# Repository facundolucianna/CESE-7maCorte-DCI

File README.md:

# CESE-7maCorte-DCI

Replica de Sparkfun ESP32 Thing. 

Basado de SparkFun ESP32 Thing (https://www.sparkfun.com/products/13907) 

Bajo Licencia Creative Commons Attributions Share-Alike 4.0 (https://creativecommons.org/licenses/by-sa/4.0/)

Modificación sin el respaldo del autor original

Atención:

Este diseño de PCB y esquematico se entrega "como está" y sin niguna garantia expresa o implícita, incluyendo, sin limitación, las garantias implícitas de comercialización y aptitude para un propósito particular.

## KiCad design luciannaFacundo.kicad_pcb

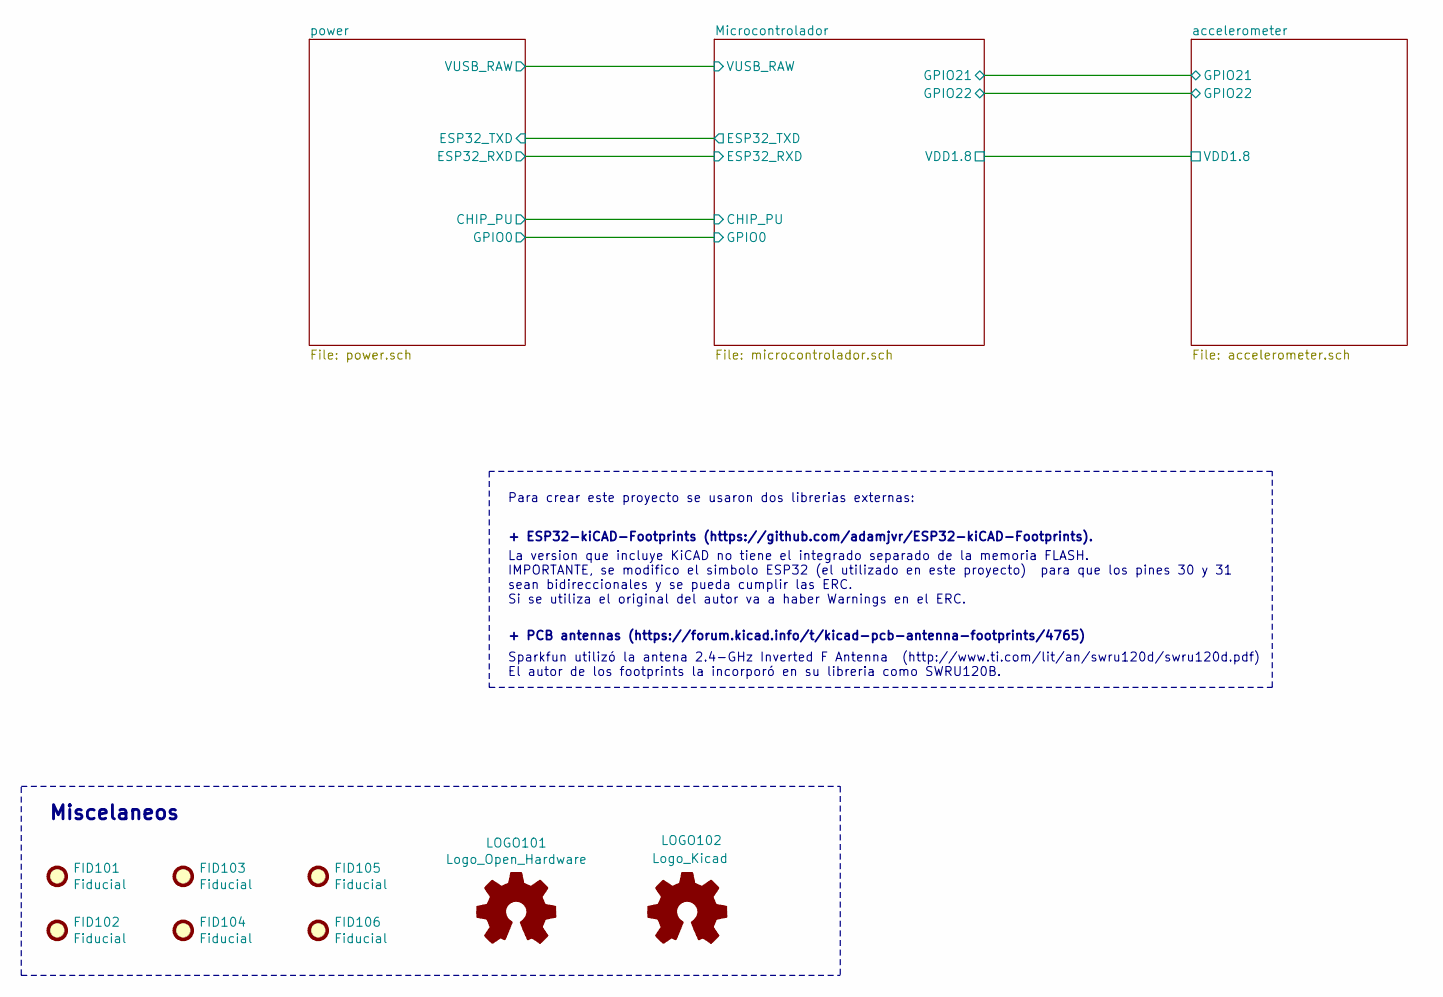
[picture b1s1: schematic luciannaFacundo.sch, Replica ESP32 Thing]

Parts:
FID101, FID102, FID103, FID104, FID105, FID106: Fiducial; Fiducial_1mm_Mask3mm
LOGO101: Logo_Open_Hardware; OSHW-Logo2_7.3x6mm_SilkScreen
LOGO102: Logo_Kicad; KiCad-Logo2_5mm_SilkScreen

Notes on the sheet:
Para crear este proyecto se usaron dos librerias externas: La version que incluye KiCAD no tiene el integrado separado de la memoria FLASH. IMPORTANTE, se modifico el simbolo ESP32 (el utilizado en este proyecto) para que los pines 30 y 31 sean bidireccionales y se pueda cumplir las ERC. Si se util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
+ ESP32-kiCAD-Footprints (https://github.com/adamjvr/ESP32-kiCAD-Footprints).
+ PCB antennas (https://forum.kicad.info/t/kicad-pcb-antenna-footprints/4765)
Miscelaneos

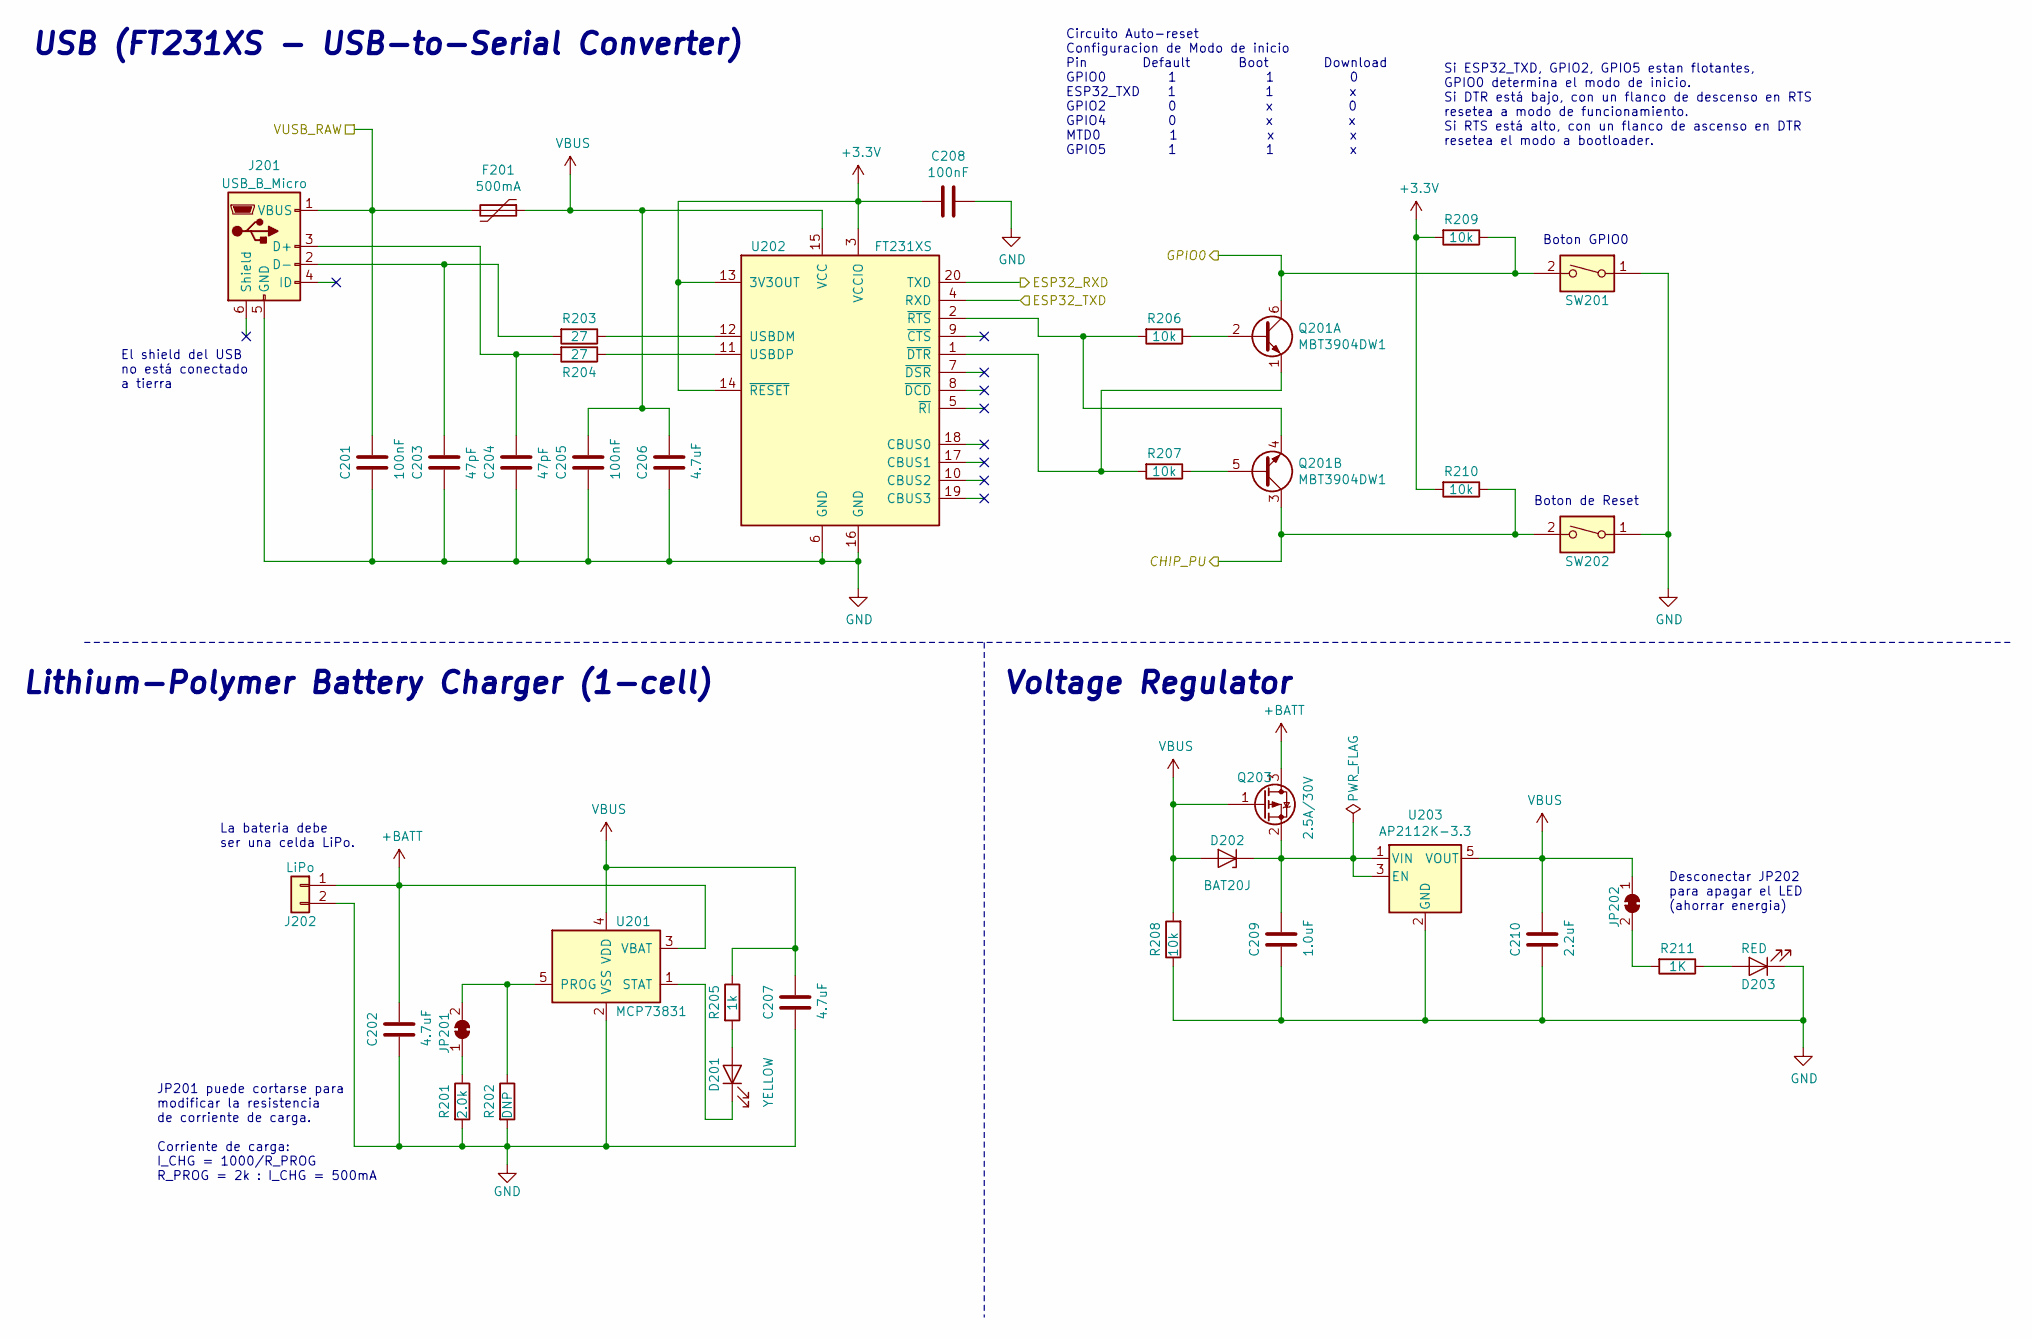
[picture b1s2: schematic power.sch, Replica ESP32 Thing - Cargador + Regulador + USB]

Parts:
C201, C205, C208: 100nF; C_0603_1608Metric
C202, C206, C207: 4.7uF; C_0603_1608Metric
C203, C204: 47pF; C_0603_1608Metric
C209: 1.0uF; C_0805_2012Metric
C210: 2.2uF; C_0603_1608Metric
D201: YELLOW; LED_0603_1608Metric
D202: BAT20J; D_SOD-323
D203: RED; LED_0603_1608Metric
F201: 500mA; Fuse_1206_3216Metric
J201: USB_B_Micro; USB_Micro-B_Wuerth_629105150521
J202: LiPo; JST_PH_S2B-PH-K_1x02_P2.00mm_Horizontal
JP201, JP202: SolderJumper_2_Bridged; SolderJumper-2_P1.3mm_Bridged2Bar_RoundedPad1.0x1.5mm
Q201: MBT3904DW1; SOT-363_SC-70-6
Q203: 2.5A/30V; SOT-23
R201: 2.0k; R_0603_1608Metric
R202: DNP; R_Axial_DIN0204_L3.6mm_D1.6mm_P5.08mm_Horizontal
R203, R204: 27; R_0603_1608Metric
R205: 1k; R_0603_1608Metric
R206, R207, R208, R209, R210: 10k; R_0603_1608Metric
R211: 1K; R_0603_1608Metric
SW201, SW202: SW_DIP_x01; SW_Push_1P1T_NO_CK_KMR2
U201: MCP73831; SOT-23-5
U202: FT231XS; SSOP-20_3.9x8.7mm_P0.635mm
U203: AP2112K-3.3; SOT-23-5

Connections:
+3V3: C208.2, R209.2, R210.2, U202.3 (VCCIO), U202.13 (3V3OUT), U202.14 (~RESET); also elsewhere on the board
+BATT: C202.1, J202.1, Q203.3 (D), U201.3 (VBAT); also elsewhere on the board
CHIP_PU: Q201.3 (C2), R210.1, SW202.2; also elsewhere on the board
ESP32_RXD: U202.20 (TXD); also elsewhere on the board
ESP32_TXD: U202.4 (RXD); also elsewhere on the board
GND: C201.2, C202.2, C203.2, C204.2, C205.2, C206.2, C207.2, C208.1, C209.2, C210.2, D203.1 (K), J201.5 (GND), J201.6 (Shield), J202.2, R201.2, R202.2, R208.1, SW201.1, SW202.1, U201.2 (VSS), U202.6 (GND), U202.16 (GND), U203.2 (GND); also elsewhere on the board
GPIO0: Q201.6 (C1), R209.1, SW201.2; also elsewhere on the board
unnamed: C203.1, J201.2 (D-), R203.2
unnamed: C204.1, J201.3 (D+), R204.2
unnamed: C209.1, D202.1 (K), Q203.2 (S), U203.1 (VIN), U203.3 (EN)
unnamed: D201.1 (K), U201.1 (STAT)
unnamed: D203.2 (A), R211.1
unnamed: JP201.1 (A), R201.1
unnamed: JP201.2 (B), R202.1, U201.5 (PROG)
unnamed: JP202.2 (B), R211.2
unnamed: Q201.1 (E1), R207.2, U202.1 (~DTR)
unnamed: Q201.2 (B1), R206.1
unnamed: Q201.4 (E2), R206.2, U202.2 (~RTS)
unnamed: Q201.5 (B2), R207.1
unnamed: R203.1, U202.12 (USBDM)
unnamed: R204.1, U202.11 (USBDP)
VUSB_RAW: C201.1, F201.2, J201.1 (VBUS); also elsewhere on the board

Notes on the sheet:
Circuito Auto-reset Configuracion de Modo de inicio Pin Default Boot Download GPIO0 1 1 0 ESP32_TXD 1 1 x GPIO2 0 x 0 GPIO4 0 x x MTD0 1 x x GPIO5 1 1 x
La bateria debe ser una celda LiPo.
JP201 puede cortarse para modificar la resistencia de corriente de carga. Corriente de carga: I_CHG = 1000/R_PROG R_PROG = 2k : I_CHG = 500mA
Desconectar JP202 para apagar el LED (ahorrar energia)
USB (FT231XS - USB-to-Serial Converter)
Lithium-Polymer Battery Charger (1-cell)
Voltage Regulator
Si ESP32_TXD, GPIO2, GPIO5 estan flotantes, GPIO0 determina el modo de inicio. Si DTR está bajo, con un flanco de descenso en RTS resetea a modo de funcionamiento. Si RTS está alto, con un flanco de ascenso en DTR resetea el modo a bootloader.
Boton GPIO0
Boton de Reset
El shield del USB no está conectado a tierra

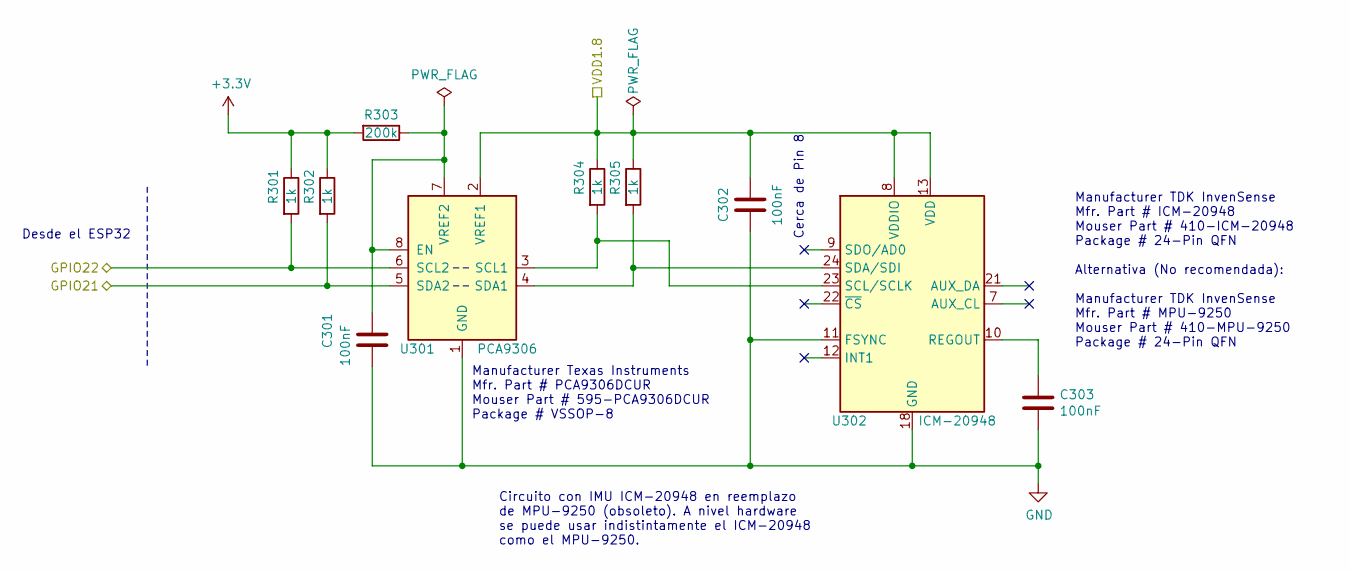
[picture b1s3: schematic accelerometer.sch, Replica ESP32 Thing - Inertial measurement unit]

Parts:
C301, C302, C303: 100nF; C_0603_1608Metric
R301, R302, R304, R305: 1k; R_0603_1608Metric
R303: 200k; R_0603_1608Metric
U301: PCA9306; VSSOP-8_2.3x2mm_P0.5mm
U302: ICM-20948; InvenSense_QFN-24_3x3mm_P0.4mm

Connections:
+3V3: R301.1, R302.1, R303.2; also elsewhere on the board
GND: C301.2, C302.2, C303.2, U301.1 (GND), U302.11 (FSYNC), U302.18 (GND), U302.20 (GND); also elsewhere on the board
GPIO21: R302.2, U301.5 (SDA2); also elsewhere on the board
GPIO22: R301.2, U301.6 (SCL2); also elsewhere on the board
unnamed: C301.1, R303.1, U301.7 (VREF2), U301.8 (EN)
unnamed: C303.1, U302.10 (REGOUT)
unnamed: R304.2, U301.3 (SCL1), U302.23 (SCL/SCLK)
unnamed: R305.2, U301.4 (SDA1), U302.24 (SDA/SDI)
VDD1.8: C302.1, R304.1, R305.1, U301.2 (VREF1), U302.8 (VDDIO), U302.13 (VDD); also elsewhere on the board

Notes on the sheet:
Cerca de Pin 8
Circuito con IMU ICM-20948 en reemplazo de MPU-9250 (obsoleto). A nivel hardware se puede usar indistintamente el ICM-20948 como el MPU-9250.
Desde el ESP32
Manufacturer Texas Instruments Mfr. Part # PCA9306DCUR Mouser Part # 595-PCA9306DCUR Package # VSSOP-8
Manufacturer TDK InvenSense Mfr. Part # ICM-20948 Mouser Part # 410-ICM-20948 Package # 24-Pin QFN Alternativa (No recomendada): Manufacturer TDK InvenSense Mfr. Part # MPU-9250 Mouser Part # 410-MPU-9250 Package # 24-Pin QFN

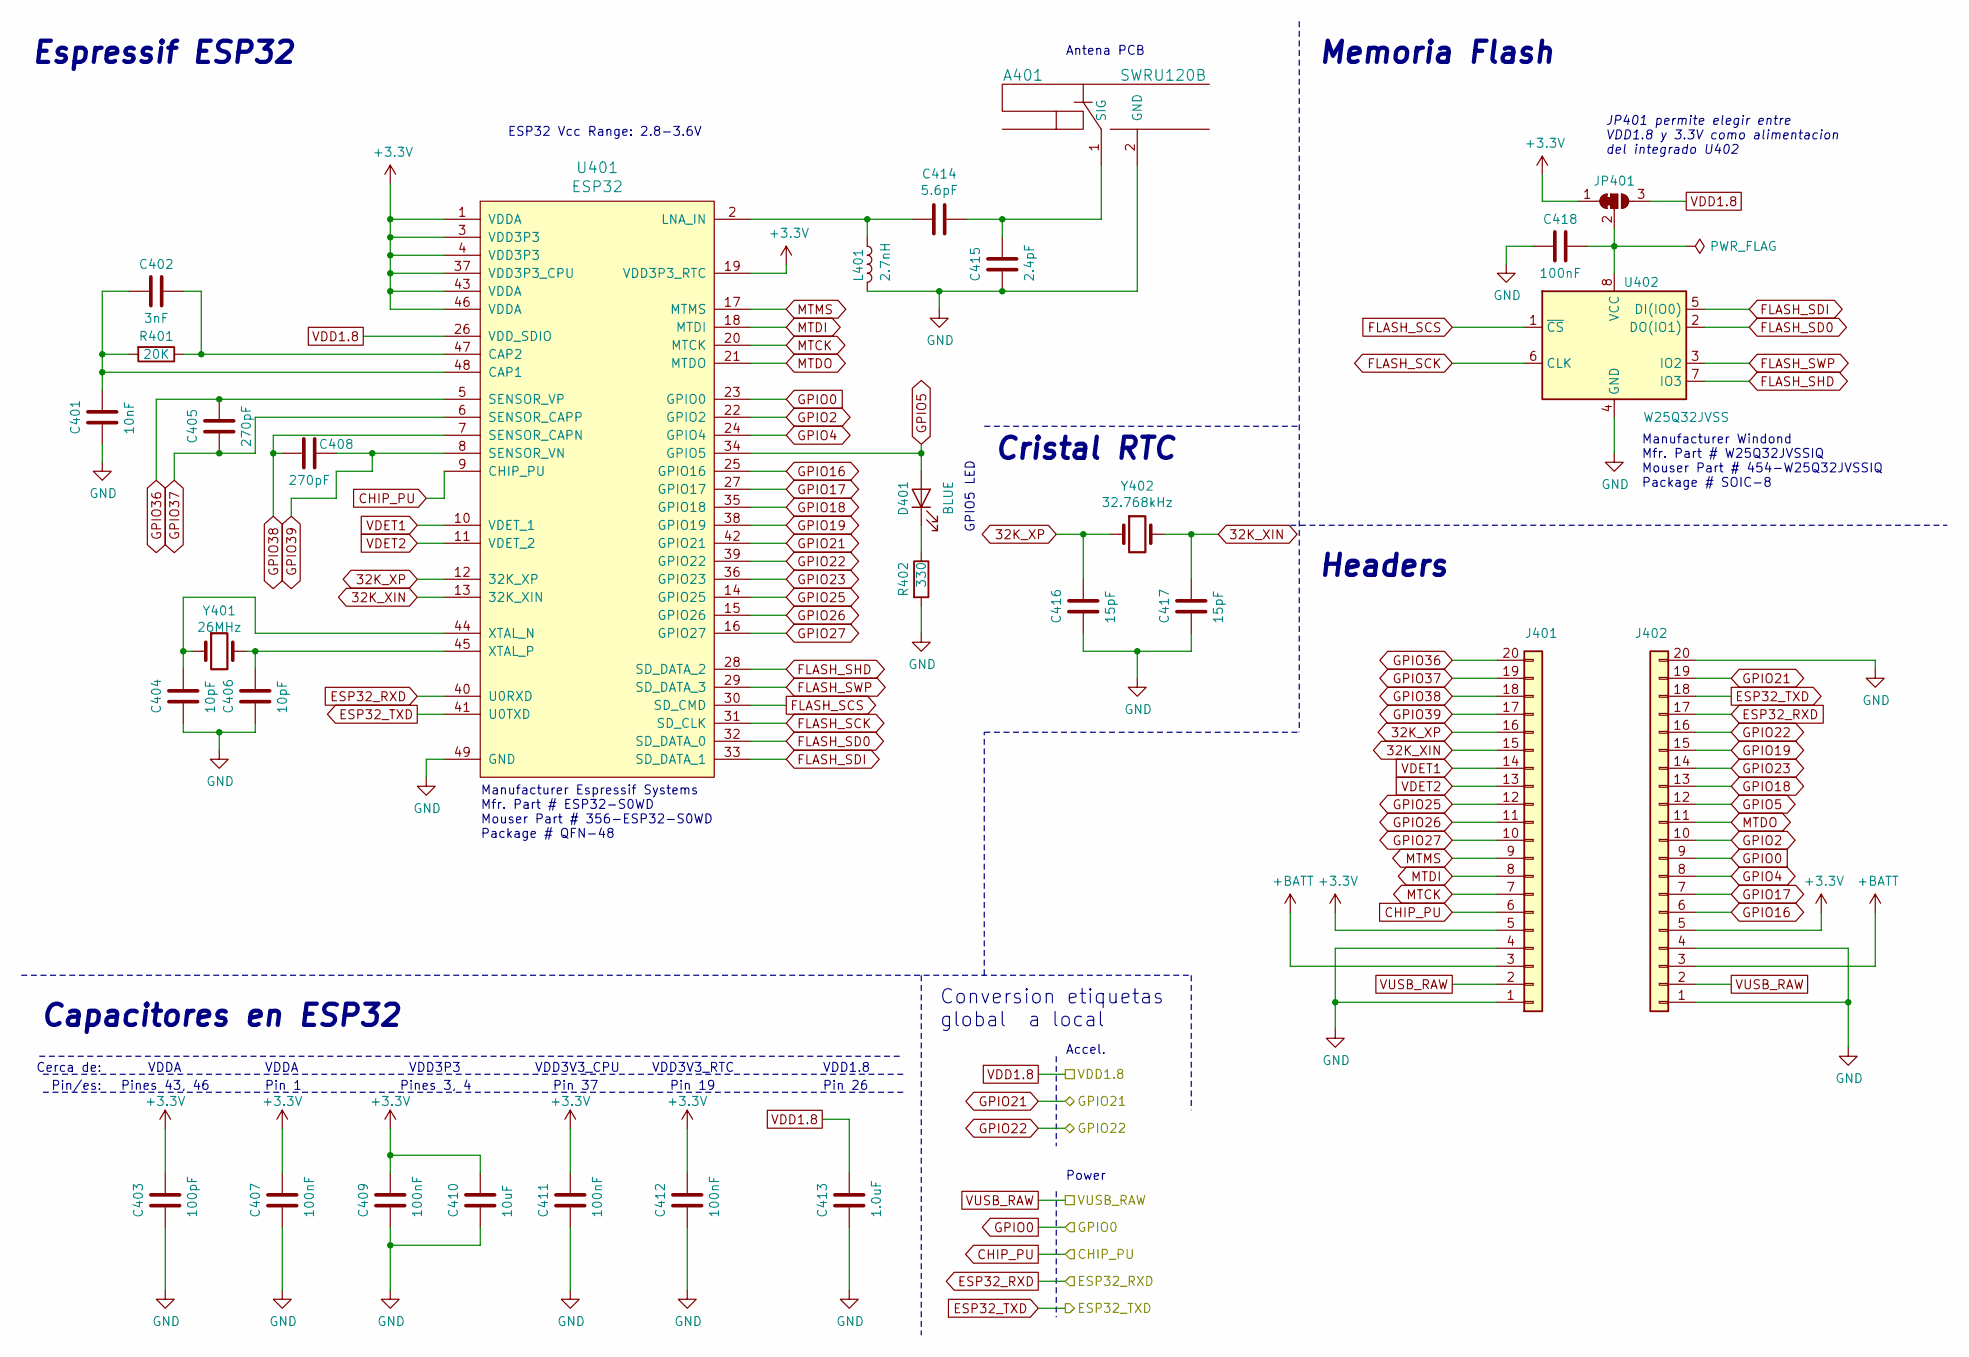
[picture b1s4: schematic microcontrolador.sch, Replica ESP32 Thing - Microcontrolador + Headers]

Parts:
A401: SWRU120B
C401: 10nF; C_0603_1608Metric
C402: 3nF; C_0603_1608Metric
C403: 100pF; C_0603_1608Metric
C404, C406: 10pF; C_0603_1608Metric
C405, C408: 270pF; C_0603_1608Metric
C407, C409, C411, C412, C418: 100nF; C_0603_1608Metric
C410: 10uF; C_0603_1608Metric
C413: 1.0uF; C_0603_1608Metric
C414: 5.6pF; C_0603_1608Metric
C415: 2.4pF; C_0603_1608Metric
C416, C417: 15pF; C_0603_1608Metric
D401: BLUE; LED_0603_1608Metric
J401, J402: Conn_01x20; PinHeader_1x20_P2.54mm_Vertical
JP401: SolderJumper_3_Bridged12; SolderJumper-3_P1.3mm_Bridged2Bar12_RoundedPad1.0x1.5mm
L401: 2.7nH; L_0603_1608Metric
R401: 20K; R_0603_1608Metric
R402: 330; R_0603_1608Metric
U401: ESP32; QFN-48-1EP_6x6mm_P0.4mm_EP4.3x4.3mm
U402: W25Q32JVSS; SOIC-8_5.23x5.23mm_P1.27mm
Y401: 26MHz; Crystal_SMD_5032-2Pin_5.0x3.2mm
Y402: 32.768kHz; Crystal_SMD_3215-2Pin_3.2x1.5mm

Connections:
32K_XIN: C417.1, J401.15, U401.13 (32K_XIN), Y402.2
32K_XP: C416.1, J401.16, U401.12 (32K_XP), Y402.1
+3V3: C403.1, C407.1, C409.1, C410.1, C411.1, C412.1, J401.5, J402.5, JP401.1 (A), U401.1 (VDDA), U401.3 (VDD3P3), U401.4 (VDD3P3), U401.19 (VDD3P3_RTC), U401.37 (VDD3P3_CPU), U401.43 (VDDA), U401.46 (VDDA); also elsewhere on the board
+BATT: J401.3, J402.3; also elsewhere on the board
CHIP_PU: J401.6, U401.9 (CHIP_PU); also elsewhere on the board
ESP32_RXD: J402.17, U401.40 (U0RXD); also elsewhere on the board
ESP32_TXD: J402.18, U401.41 (U0TXD); also elsewhere on the board
FLASH_SCK: U401.31 (SD_CLK), U402.6 (CLK)
FLASH_SCS: U401.30 (SD_CMD), U402.1 (~CS)
FLASH_SD0: U401.32 (SD_DATA_0), U402.2 (DO(IO1))
FLASH_SDI: U401.33 (SD_DATA_1), U402.5 (DI(IO0))
FLASH_SHD: U401.28 (SD_DATA_2), U402.7 (IO3)
FLASH_SWP: U401.29 (SD_DATA_3), U402.3 (IO2)
GND: A401.2 (GND), C401.2, C403.2, C404.1, C406.2, C407.2, C409.2, C410.2, C411.2, C412.2, C413.2, C415.2, C416.2, C417.2, C418.2, J401.1, J401.4, J402.1, J402.4, J402.20, L401.2, R402.2, U401.49 (GND), U402.4 (GND); also elsewhere on the board
GPIO0: J402.9, U401.23 (GPIO0); also elsewhere on the board
GPIO2: J402.10, U401.22 (GPIO2)
GPIO4: J402.8, U401.24 (GPIO4)
GPIO5: D401.2 (A), J402.12, U401.34 (GPIO5)
GPIO16: J402.6, U401.25 (GPIO16)
GPIO17: J402.7, U401.27 (GPIO17)
GPIO18: J402.13, U401.35 (GPIO18)
GPIO19: J402.15, U401.38 (GPIO19)
GPIO21: J402.19, U401.42 (GPIO21); also elsewhere on the board
GPIO22: J402.16, U401.39 (GPIO22); also elsewhere on the board
GPIO23: J402.14, U401.36 (GPIO23)
GPIO25: J401.12, U401.14 (GPIO25)
GPIO26: J401.11, U401.15 (GPIO26)
GPIO27: J401.10, U401.16 (GPIO27)
GPIO36: C405.2, J401.20, U401.5 (SENSOR_VP)
GPIO37: C405.1, J401.19, U401.6 (SENSOR_CAPP)
GPIO38: C408.1, J401.18, U401.7 (SENSOR_CAPN)
GPIO39: C408.2, J401.17, U401.8 (SENSOR_VN)
MTCK: J401.7, U401.20 (MTCK)
MTDI: J401.8, U401.18 (MTDI)
MTDO: J402.11, U401.21 (MTDO)
MTMS: J401.9, U401.17 (MTMS)
unnamed: A401.1 (SIG), C414.1, C415.1
unnamed: C401.1, C402.2, R401.2, U401.48 (CAP1)
unnamed: C402.1, R401.1, U401.47 (CAP2)
unnamed: C404.2, U401.44 (XTAL_N), Y401.1
unnamed: C406.1, U401.45 (XTAL_P), Y401.2
unnamed: C414.2, L401.1, U401.2 (LNA_IN)
unnamed: C418.1, JP401.2 (C), U402.8 (VCC)
unnamed: D401.1 (K), R402.1
VDD1.8: C413.1, JP401.3 (B), U401.26 (VDD_SDIO); also elsewhere on the board
VDET1: J401.14, U401.10 (VDET_1)
VDET2: J401.13, U401.11 (VDET_2)
VUSB_RAW: J401.2, J402.2; also elsewhere on the board

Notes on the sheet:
VDDA
Pin 37
VDD3V3_CPU
Pines 3, 4
VDD3P3
VDD3V3_RTC
Pin 19
Cerca de:
Pin/es:
Pin 1
Pines 43, 46
Capacitores en ESP32
Espressif ESP32
Cristal RTC
Memoria Flash
Headers
JP401 permite elegir entre VDD1.8 y 3.3V como alimentacion del integrado U402
ESP32 Vcc Range: 2.8-3.6V
GPIO5 LED
VDD1.8
Pin 26
Antena PCB
Manufacturer Espressif Systems Mfr. Part # ESP32-S0WD Mouser Part # 356-ESP32-S0WD Package # QFN-48
Manufacturer Windond Mfr. Part # W25Q32JVSSIQ Mouser Part # 454-W25Q32JVSSIQ Package # SOIC-8
Conversion etiquetas global a local
Power
Accel.

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
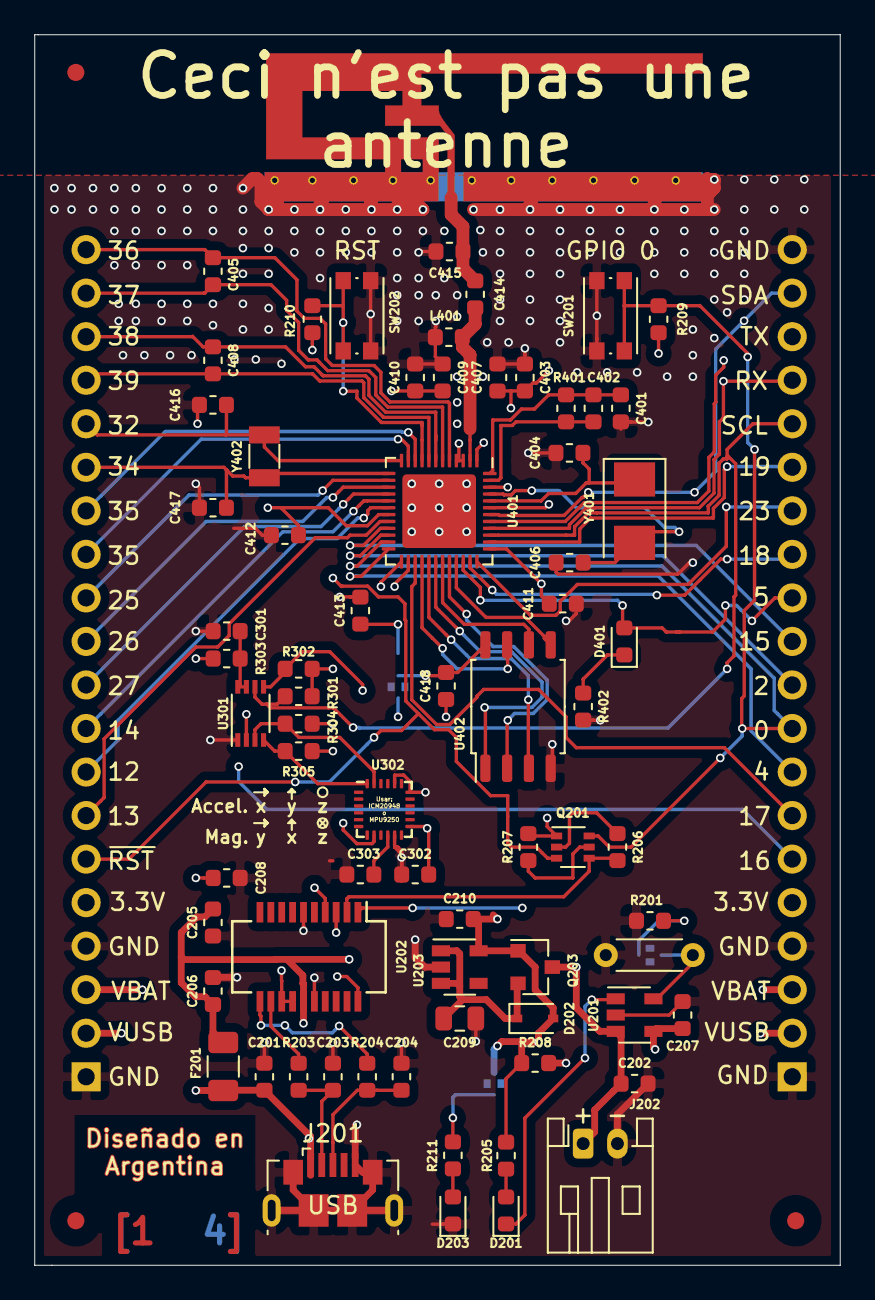
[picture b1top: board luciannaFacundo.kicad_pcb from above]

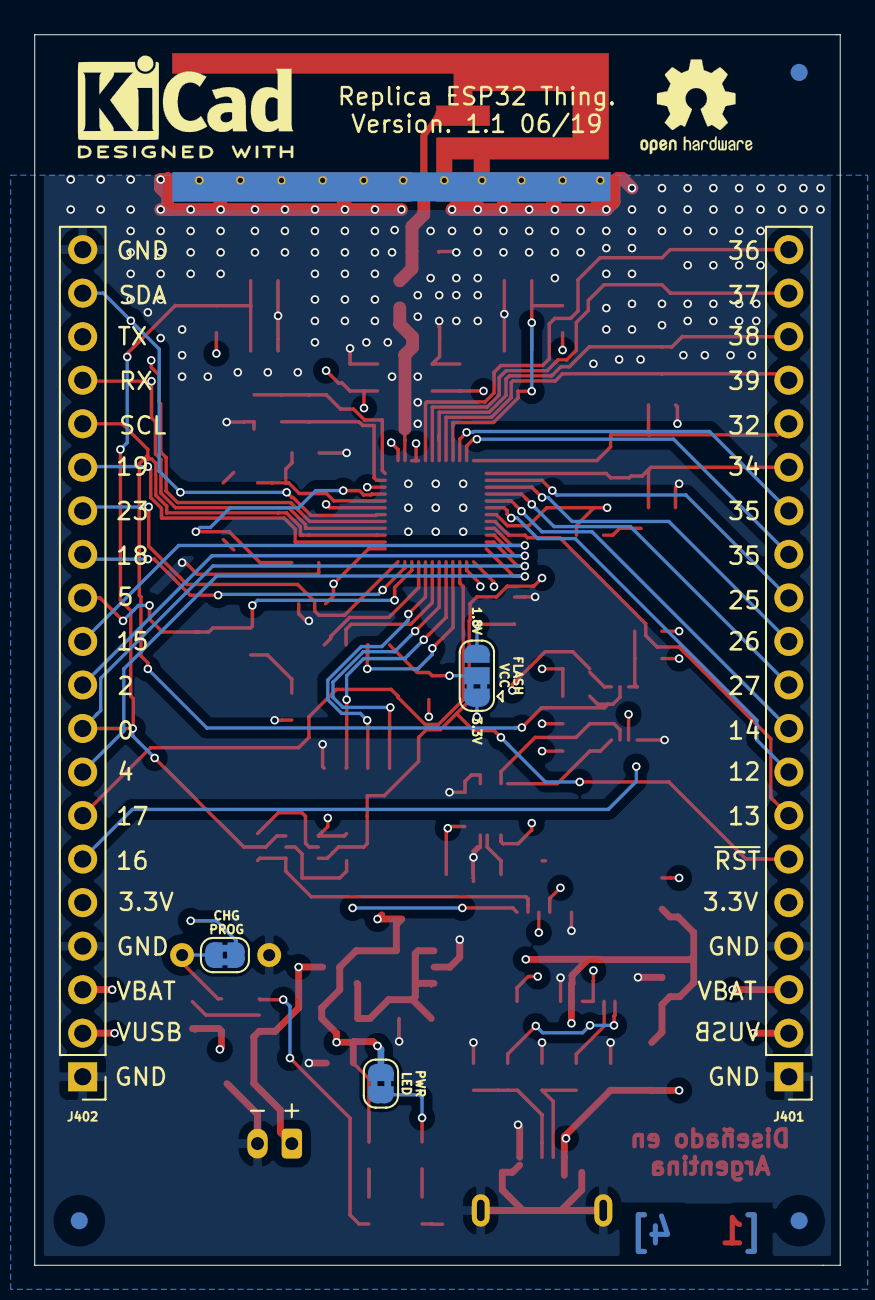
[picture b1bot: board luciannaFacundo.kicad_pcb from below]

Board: 4 copper layers, 47.0 x 71.8 mm, 84 parts (10 on the bottom side), 68 nets.

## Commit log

2019-06-17 PMD01 - Esquematico y footprints asignados
2019-06-17 PMD02 - Agregado de documentacion y PDF
2019-06-18 PMD03 - Creacion PCB y modelo 3D
2019-06-25 Correcciones
2019-06-25 Cambio en esquematico
